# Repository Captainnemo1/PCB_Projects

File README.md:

# PCB_Projects
This repo consists of various PCBs made by me 
They have been labeled as per the name of the project

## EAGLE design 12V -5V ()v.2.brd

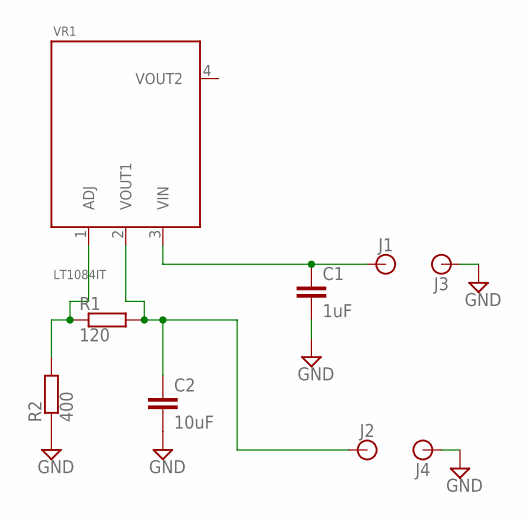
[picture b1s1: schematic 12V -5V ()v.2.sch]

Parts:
C1: 1uF; C0805
C2: 10uF; C0805
J1, J2, J3, J4: BANANA_CONN
R1: 120; R0805
R2: 400; R0805
VR1: LT1084IT

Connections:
GND: C1.2, C2.2, J3.P$1, J4.P$1, R2.1
unnamed: R1.1, R2.2, VR1.1 (ADJ)
VIN: C1.1, J1.P$1, VR1.3 (VIN)
VOUT: C2.1, J2.P$1, R1.2, VR1.2 (VOUT1)

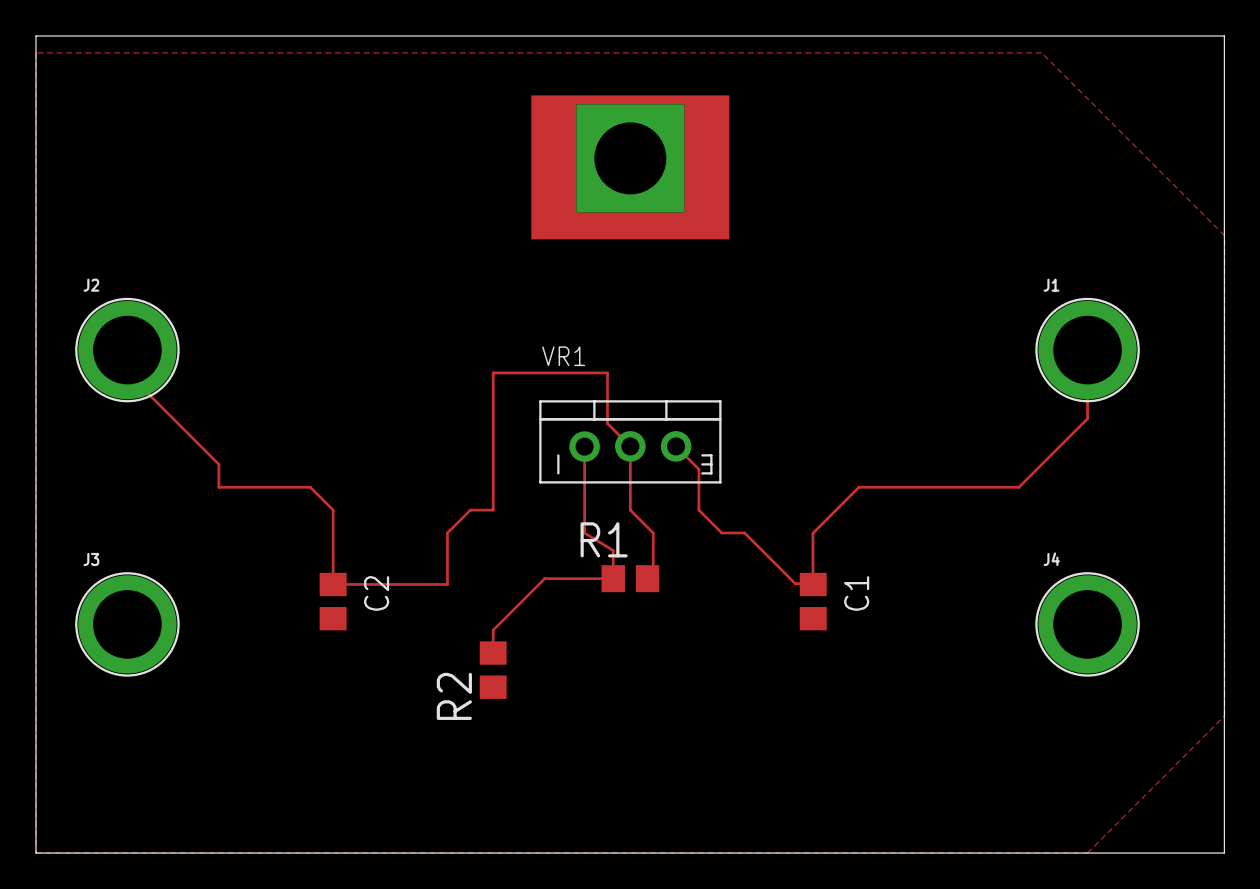
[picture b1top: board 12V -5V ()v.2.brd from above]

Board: 2 copper layers, 66.0 x 45.4 mm, 9 parts (0 on the bottom side), 4 nets.

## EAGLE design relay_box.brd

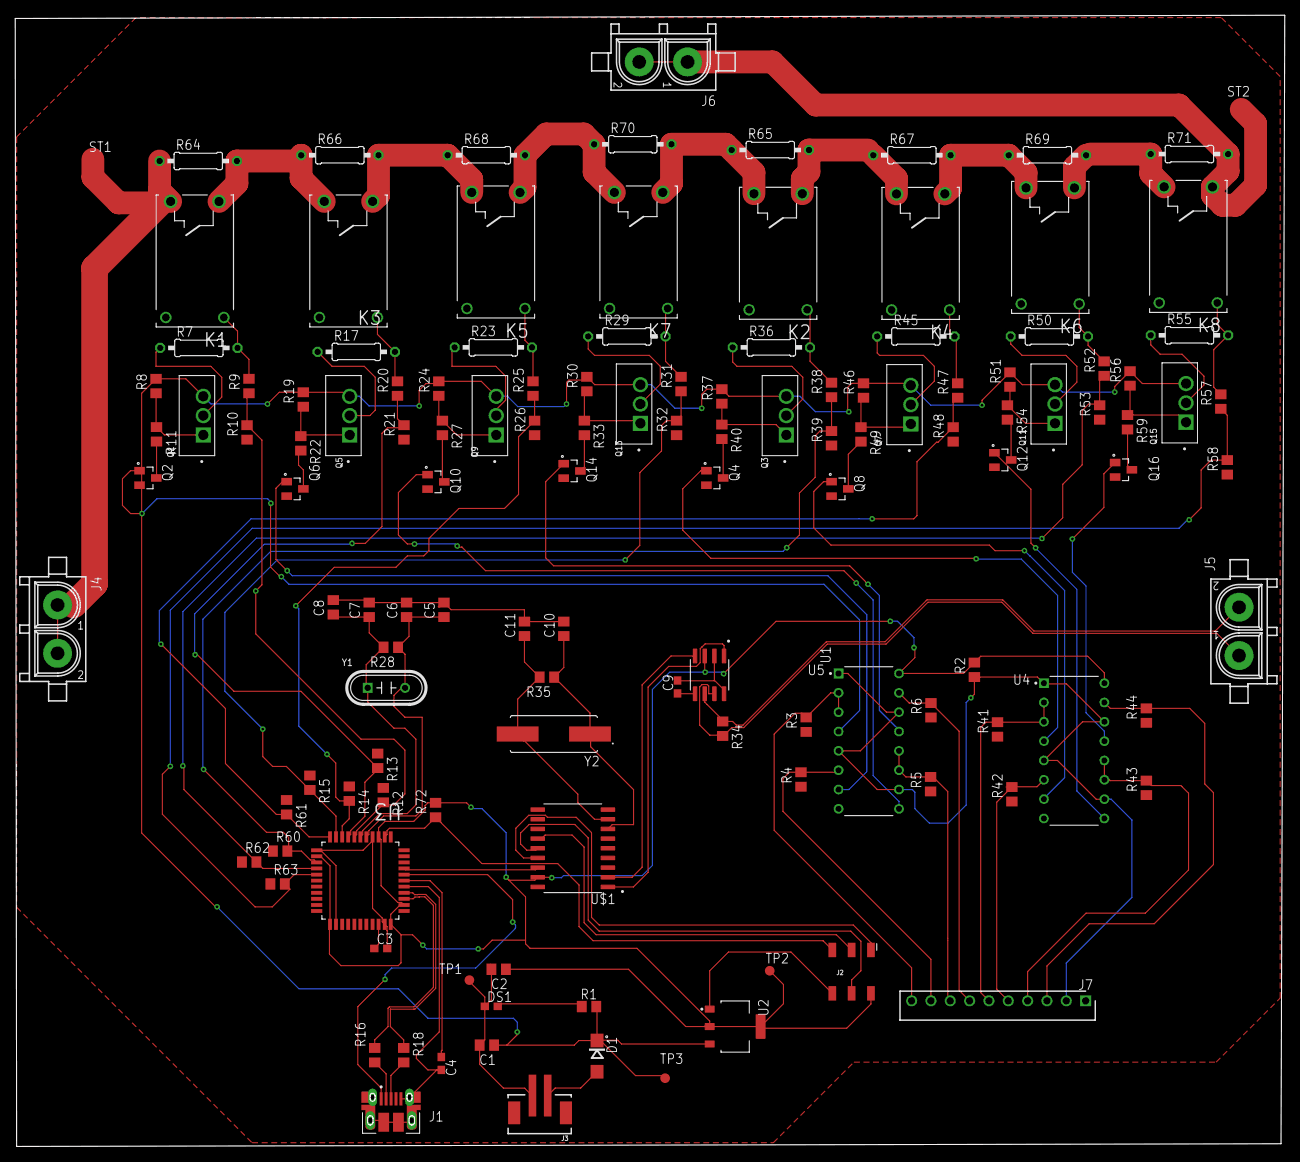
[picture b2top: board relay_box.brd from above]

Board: 2 copper layers, 166.8 x 148.6 mm, 129 parts (0 on the bottom side), 93 nets.

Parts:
C1, C2, C5, C6, C7, C8, C10, C11: 10uF; C0805
C3, C4: 1uF; C0603
C9: 22uF; C0603
D1: SS12-TP; DO214AC
DS1: LTST-C190TBKT; 0603
J1: 10103594-0001LF; AMPHENOL_10103594-0001LF
J2: 2X3_SMD
J3: JST-2-SMD-VERT
J4, J5, J6: 350428-1
J7: 5-534237-8; RHDR10W76P0X254_1X10_2540X356X
K1, K2, K3, K4, K5, K6, K7, K8: JV-5S-KT; JV-KT
Q1, Q3, Q5, Q7, Q9, Q11, Q13, Q15: IRF9540; TO254P1052X465X1989-3
Q2, Q4, Q6, Q8, Q10, Q12, Q14, Q16: MMBT3904LT1G; SOT23
R1: 560R; R0805
R2, R3, R4, R5, R6, R12, R13, R14, R15, R41, R42, R43, R44, R60, R61, R62, R63, R72: 10k; R0805
R7, R17, R23, R29, R36, R45, R50, R55: 560R; 0207/10
R8, R10, R19, R21, R24, R26, R30, R32, R37, R39, R46, R48, R51, R53, R56, R58: 12K; R0805
R9, R11, R20, R22, R25, R27, R31, R33, R38, R40, R47, R49, R52, R54, R57, R59: 18K; R0805
R16, R18: 22R; R0805
R28, R35: 1M; R0805
R34: 120R; R0805
R64, R65, R66, R67, R68, R69, R70, R71: 0R; 0207/10
ST1, ST2: TPB1,27; B1,27
TP1, TP2, TP3: TPB1,27; B1,27
U1: TJA1050T/CM,118; SOIC127P600X175-8N
U2: AMS1117-5.0; SOT229P700X180-4N
U3: ATMEGA32U4-AU; QFP80P1200X1200X120-44N
U4, U5: SN74LS279AN; DIP794W45P254L1969H508Q16
U$1: MCP2515-I/SO; SOIC127P1030X265-18N
Y1: 49S/18PF; XTAL_49S/18PF
Y2: FOXSDLF/080-20; XTAL1170X500X450

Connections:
1Q: Q2.1, U5.4
1S: J7.10, R3.2, U5.2, U5.3
2Q: Q6.1, U5.7
2S: J7.9, R4.2, U5.6
3Q: Q10.1, U5.9
3S: J7.8, R5.2, U5.11, U5.12
4Q: Q14.1, U5.13
4S: J7.7, R6.2, U5.15
5Q: Q4.1, U4.4
5S: J7.6, R41.2, U4.2, U4.3
6Q: Q8.1, U4.7
6S: J7.5, R42.2, U4.6
7Q: Q12.1, U4.9
7S: J7.4, R43.2, U4.11, U4.12
8Q: Q16.1, U4.13
8S: J7.3, R44.2, U4.15
+5V: C2.1, J2.2, R2.2, R72.2, TP2.TP, U1.3, U2.2, U2.4, U3.2, U3.14, U3.24, U3.34, U3.44, U4.16, U5.16, U$1.17
CAN_N: J5.2, R34.1, U1.6
CAN_P: J5.1, R34.2, U1.7
D_N: R16.1, U3.3
D_P: R18.1, U3.4
GND: C1.2, C2.2, C3.2, C5.2, C6.2, C7.2, C8.2, C9.2, C10.2, C11.2, DS1.1, J2.6, J3.GND, K1.4, K2.4, K3.4, K4.4, K5.4, K6.4, K7.4, K8.4, Q2.2, Q4.2, Q6.2, Q8.2, Q10.2, Q12.2, Q14.2, Q16.2, R3.1, R4.1, R5.1, R6.1, R10.1, R12.1, R13.1, R14.1, R15.1, R21.1, R26.1, R32.1, R39.1, R41.1, R42.1, R43.1, R44.1, R48.1, R53.1, R58.1, R60.1, R61.1, R62.1, R63.1, TP1.TP, U1.2, U1.8, U2.1, U3.15, U3.23, U3.35, U3.43, U4.8, U5.8, U$1.9
HVD: J4.1, J4.2, K1.3, R64.1, ST1.TP
MISO: J2.1, U$1.15
MOSI: J2.4, U$1.14
unnamed: Q1.1, R8.1, R11.1
unnamed: Q1.2, R7.1
unnamed: Q2.3, R11.2
unnamed: K1.1, R7.2, R9.2
unnamed: Q3.1, R37.1, R40.1
unnamed: Q4.3, R40.2
unnamed: K2.1, R36.2, R38.2
unnamed: Q3.2, R36.1
unnamed: Q5.1, R19.1, R22.1
unnamed: Q6.3, R22.2
unnamed: K3.1, R17.2, R20.2
unnamed: Q5.2, R17.1
unnamed: Q7.1, R46.1, R49.1
unnamed: Q8.3, R49.2
unnamed: K4.1, R45.2, R47.2
unnamed: Q7.2, R45.1
unnamed: Q9.1, R24.1, R27.1
unnamed: Q10.3, R27.2
unnamed: K5.1, R23.2, R25.2
unnamed: Q9.2, R23.1
unnamed: Q11.1, R51.1, R54.1
unnamed: Q12.3, R54.2
unnamed: K6.1, R50.2, R52.2
unnamed: Q11.2, R50.1
unnamed: Q13.1, R30.1, R33.1
unnamed: Q14.3, R33.2
unnamed: K7.1, R29.2, R31.2
unnamed: Q13.2, R29.1
unnamed: Q15.1, R56.1, R59.1
unnamed: Q16.3, R59.2
unnamed: K8.1, R55.2, R57.2
unnamed: Q15.2, R55.1
unnamed: DS1.2, R1.1
unnamed: D1.A, J3.VCC
unnamed: J1.2, R16.2
unnamed: J1.3, R18.2
unnamed: C9.1, U1.5
unnamed: C3.1, U3.42
OSC1: C11.1, R35.2, U$1.8, Y2.2
OSC2: C10.1, R35.1, U$1.7, Y2.1
PD0: R9.1, R10.2, R12.2, U3.18
PD1: R13.2, R20.1, R21.2, U3.19
PD2: R14.2, R25.1, R26.2, U3.20
PD3: R15.2, R31.1, R32.2, U3.21
PD4: R38.1, R39.2, R60.2, U3.25
PD5: R47.1, R48.2, R61.2, U3.22
PD6: R52.1, R53.2, R62.2, U3.26
PD7: R57.1, R58.2, R63.2, U3.27
R: J7.2, R2.1, U4.1, U4.5, U4.10, U4.14, U5.1, U5.5, U5.10, U5.14
RELAY1: K1.2, K3.3, R64.2, R66.1
RELAY2: K3.2, K5.3, R66.2, R68.1
RELAY3: K5.2, K7.3, R68.2, R70.1
RELAY4: K2.3, K7.2, R65.1, R70.2
RELAY5: K2.2, K4.3, R65.2, R67.1
RELAY6: K4.2, K6.3, R67.2, R69.1
RELAY7: K6.2, K8.3, R69.2, R71.1
RELAY8: J6.1, J6.2, K8.2, R71.2, ST2.TP
RST: J2.5, R72.1, U3.13
RX_CAN: U1.4, U$1.2
SCLK: J2.3, U$1.13
SS: U3.8, U$1.16
TX_CAN: U1.1, U$1.1
UCAP: C4.1, U3.6
UGND: C4.2, J1.5, J1.6, J1.7, J1.8, J1.9, J1.10, J1.11, J1.S1, J1.S2, U3.5
VBUS: J1.1, U3.7
VCC: C1.1, D1.C, Q1.3, Q3.3, Q5.3, Q7.3, Q9.3, Q11.3, Q13.3, Q15.3, R1.2, R8.2, R19.2, R24.2, R30.2, R37.2, R46.2, R51.2, R56.2, TP3.TP, U2.3
XTAL1: C7.1, C8.1, R28.2, U3.17, Y1.1
XTAL2: C5.1, C6.1, R28.1, U3.16, Y1.2

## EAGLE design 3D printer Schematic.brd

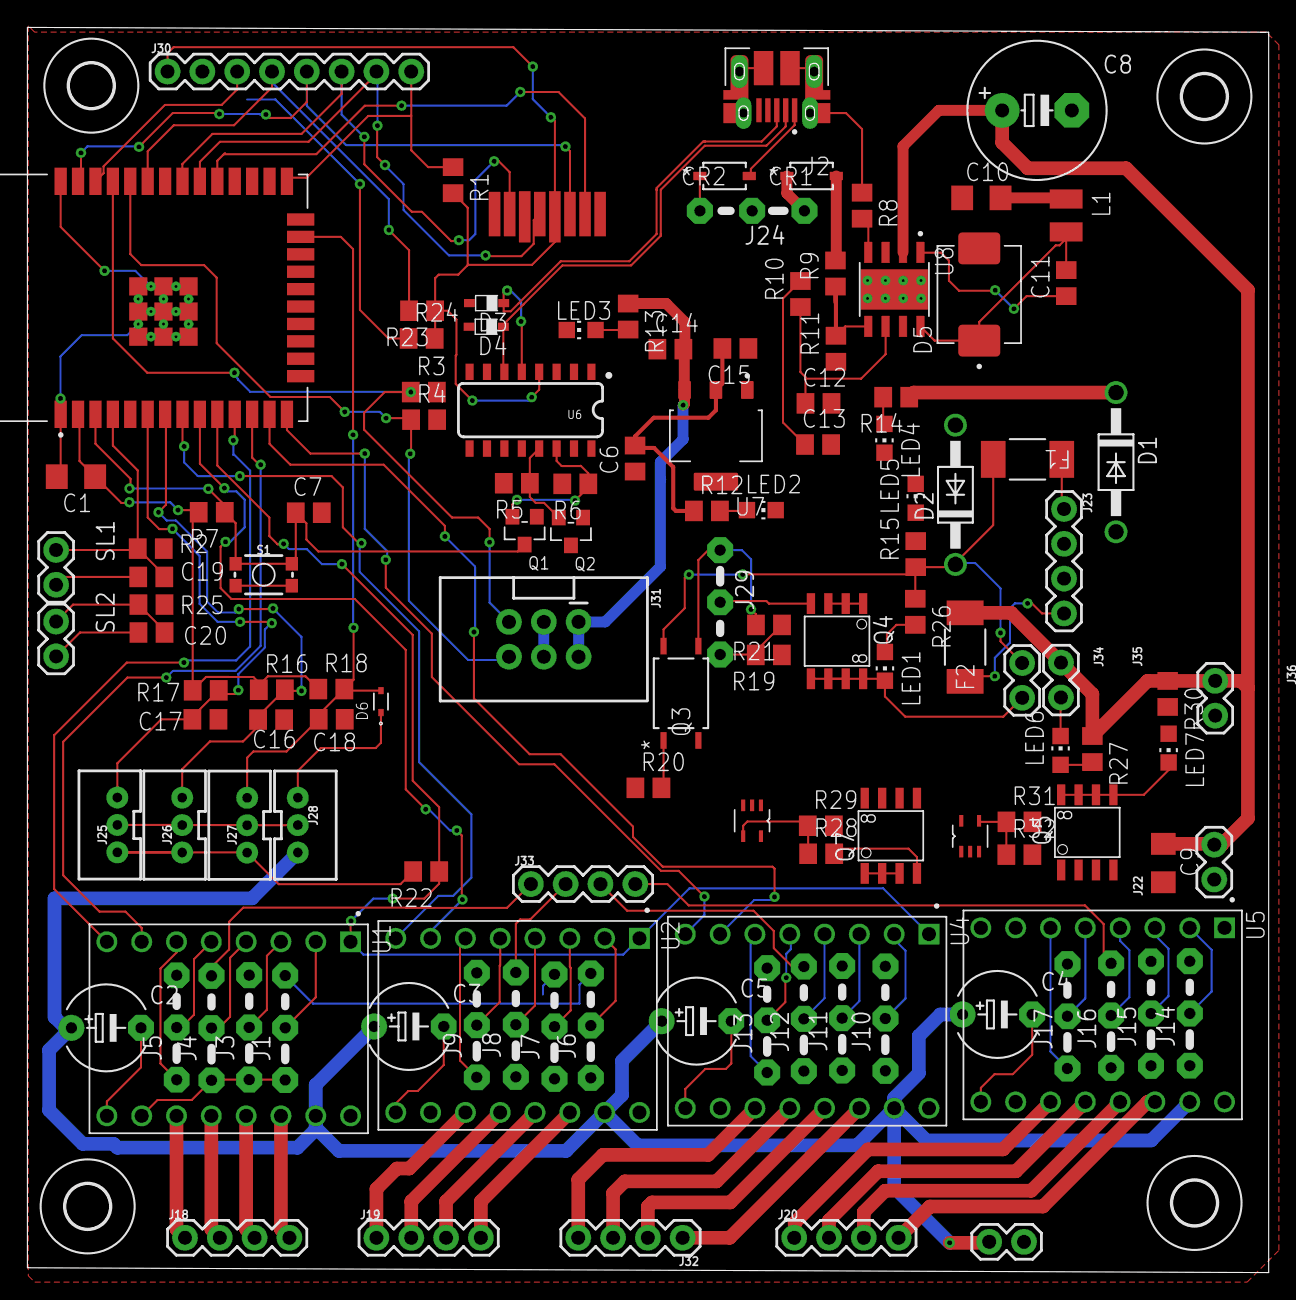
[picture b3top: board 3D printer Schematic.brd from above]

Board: 2 copper layers, 90.6 x 90.9 mm, 130 parts (1 on the bottom side), 112 nets.

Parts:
A1, A2: 74LVC1G125DCKRG4; DCK5_TEX
B2: MICRO-SDCARD
C1: 100uF 6.3V; C1206
C2, C3, C4, C5: 100uF35V; E5-6
C6: 10nF50V; C0805
C7: 100uF25V; C0805
C8: 100uF50V; E5-10,5
C9: 4.7uF50V; C1206
C10: 47uF16V; C1206
C11: 100nF50V; C0805
C12: 56pF50V; C0805
C13: 820pF50V; C0805
C14, C15: 47uF6.3V; C0805
C16, C17, C18: 100nF25V; C0805
C19, C20: 22uF6.3V; C0805
CR1, CR2: CR_19WLC_LTO
D1, D2: 1N4004; DO41-10
D3, D4: PESD5V0S1BA; SOD323
D5: B540C-13-F; DIOM6959X245N
D6: 1N4148WT; SODFL1608X70N
F1: 15A 2410; 0453SERIES_LTF
F2: 30A 3912; 0453SERIES_LTF
H1, H2, H3, H4: MOUNT-HOLE3.2; 3,2
J1, J3, J4, J5, J6, J7, J8, J9, J10, J11, J12, J13, J14, J15, J16, J17, J24, J29: 04C
J2: 10103594-0001LF; AMPHENOL_10103594-0001LF
J18, J19, J20, J23: 1X04
J21: Fan_case; 1X02
J22: FAN_HEATSINK; 1X02
J25, J26, J27, J28: JST-3-PTH-VERT
J30: 1X08
J31: 2X3-SHROUDED
J32: Z_Motor; 1X04
J33: CS_PINS; 1X04
J34: BED; 1X02
J35: E0; 1X02
J36: PART_FAN; 1X02
L1: 4.7uH4.5A; L2825P
LED1: LED_BED; CHIP-LED0805
LED2: LED_3V; CHIP-LED0805
LED3: LED_5V; CHIP-LED0805
LED4: LED_VIN; CHIP-LED0805
LED5: LED_VBED; CHIP-LED0805
LED6: LED_E0; CHIP-LED0805
LED7: LED_FAN; CHIP-LED0805
Q1, Q2: SMD-TRANSISTOR-NPN-50V-100MA(SOT-23); SOT-23
Q3: TLP182(E; 4PIN_SO6_TOS
Q4, Q5, Q7: FDS5680; SO-8
R1, R16, R17, R18, R22, R23, R24: 10K; R0805
R2, R25: 4.7K; R0805
R3, R4: 0R; R0805
R5, R6, R7: 12K; R0805
R8, R12, R13, R14, R15: 73.2K; R0805
R9: 60.4K; R0805
R10: 23.7K; R0805
R11: 11.5K; R0805
R19, R21: 1K; R0805
R20: 330R; R0805
R26, R27, R30: 2.2K; R0805
R28, R31: 10R; R0805
R29, R32: 100K; R0805
S1: TACTILE_SWITCH_SMD_4.6X2.8MM
SL1: T_E0; 1X02
SL2: T_BED; 1X02
U1, U2, U4, U5: A4988_STEPPER_MOTOR_DRIVER_CARRIER; MODULE_A4988_STEPPER_MOTOR_DRIVER_CARRIER
U3: ESP32-WROOM-32D; MODULE_ESP32-WROOM-32D
U6: CH340C; SO016
U7: AMS1117-3.3; SOT229P700X180-4N
U8: TPS54340DDA; VREG_LM5017MR/NOPB

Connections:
0: D1.A, J23.2, R19.1
3.3V: B2.VCC, C1.1, C6.2, C15.2, J1.1, J3.1, J4.1, J6.1, J7.1, J8.1, J10.1, J11.1, J12.1, J14.1, J15.1, J16.1, J25.1, J26.1, J27.1, J30.1, R1.2, R7.2, R12.1, R16.1, R17.1, R18.1, R22.2, R23.1, R24.2, U1.10, U2.10, U3.2, U4.10, U5.10, U6.4, U6.16, U7.2
5V1: C10.2, CR1.2, L1.1, R9.2
+5V: A1.5, A2.5, C14.2, J24.2, J31.1, J31.2, R2.2, R13.1, R25.2, U7.3
COMP: C12.1, R10.1, U8.6
DTR: Q2.2, R5.1, U6.13
D_N: D4.C, J2.2, U6.6
D_P: D3.C, J2.3, U6.5
E0_CS: J16.3, J33.4
E0_DIR_PIN: U3.28, U5.8
E0_MS1: J14.2, U5.2
E0_MS2: J15.2, U5.3
E0_MS3: J16.2, U5.4
E0_RST: J17.2, U5.5
E0_SLP: J17.1, U5.6
E0_STEP_PIN: U3.27, U5.7
EN: C7.1, Q1.3, R7.1, S1.3, S1.4, U3.3
FAN_E0_PIN: A2.2, U3.16
FB: R9.1, R11.2, U8.5
GND: A1.1, A1.3, A2.1, A2.3, B2.GND, C1.2, C2.-, C3.-, C4.-, C5.-, C6.1, C7.2, C8.-, C9.2, C10.1, C12.2, C13.2, C14.1, C15.1, C16.2, C17.2, C18.2, C19.1, C20.1, D2.A, D3.A, D4.A, D5.A, J2.5, J2.6, J2.7, J2.8, J2.9, J2.10, J2.11, J2.S1, J2.S2, J21.1, J22.1, J23.3, J25.2, J26.2, J27.2, J28.2, J31.3, J31.4, LED2.C, LED3.C, LED4.C, LED5.C, Q3.3, Q4.1, Q4.2, Q4.3, Q5.1, Q5.2, Q5.3, Q7.1, Q7.2, Q7.3, R8.1, R11.1, R29.2, R32.2, S1.1, S1.2, SL1.2, SL2.2, U1.9, U1.16, U2.9, U2.16, U3.1, U3.15, U3.38, U3.39_1, U3.39_2, U3.39_3, U3.39_4, U3.39_5, U3.39_6, U3.39_7, U3.39_8, U3.39_9, U3.39_10, U3.39_11, U3.39_12, U3.39_13, U3.39_14, U3.39_15, U3.39_16, U3.39_17, U3.39_18, U3.39_19, U3.39_20, U3.39_21, U4.9, U4.16, U5.9, U5.16, U6.1, U7.1, U8.7, U8.9
HEATER_BED_PIN: R20.1, U3.26
HEATER_E0_PIN: A1.2, U3.24
IO0: J30.8, Q2.3, R1.1, U3.25
MISO: B2.DAT0, J5.3, J9.3, J13.3, J17.3, J30.6, U3.31
MOSI: B2.CMD, J1.3, J6.3, J10.3, J14.3, J30.5, U3.37
MOTOR_EN_PIN: R22.1, U1.1, U2.1, U3.10, U4.1, U5.1
unnamed: J36.2, LED7.C, Q5.5, Q5.6, Q5.7, Q5.8
unnamed: LED7.A, R30.2
unnamed: J18.1, U1.11
unnamed: J18.2, U1.12
unnamed: J18.3, U1.13
unnamed: J18.4, U1.14
unnamed: Q1.1, R5.2
unnamed: Q2.1, R6.2
unnamed: F1.1, J23.1
unnamed: F2.1, J23.4
unnamed: LED2.A, R12.2
unnamed: R3.2, U6.3
unnamed: R4.2, U6.2
unnamed: R8.2, U8.4
unnamed: LED3.A, R13.2
unnamed: C13.1, R10.2
unnamed: C11.1, U8.1
unnamed: C11.2, D5.C, L1.2, U8.8
unnamed: LED4.A, R14.2
unnamed: J19.1, U2.11
unnamed: J19.2, U2.12
unnamed: J19.3, U2.13
unnamed: J19.4, U2.14
unnamed: J20.1, U5.11
unnamed: J20.2, U5.12
unnamed: J20.3, U5.13
unnamed: J20.4, U5.14
unnamed: LED5.A, R15.2
unnamed: CR1.1, J24.1
unnamed: CR2.1, J24.3
unnamed: D6.C, J28.1
unnamed: Q3.1, R20.2
unnamed: Q5.4, R31.2
unnamed: J29.1, Q3.4, R21.2
unnamed: LED1.A, R26.2
unnamed: J29.3, R19.2, R21.1
unnamed: J34.2, LED1.C, Q4.5, Q4.6, Q4.7, Q4.8
unnamed: LED6.A, R27.2
unnamed: J35.2, LED6.C, Q7.5, Q7.6, Q7.7, Q7.8
unnamed: Q7.4, R28.2
RTS: Q1.2, R6.1, U6.14
SCK: B2.CLK, J3.3, J7.3, J11.3, J15.3, J30.7, U3.30
SCL: J30.3, R24.1, U3.36
SDA: J30.4, R23.2, U3.33
SS: B2.CD/DAT3, U3.29
TEMP_BED_PIN: C20.2, R25.1, SL2.1, U3.5
TEMP_E0_PIN: C19.2, R2.1, SL1.1, U3.4
TO_FAN_E0: A2.4, R31.1, R32.1
TO_HEATER_BED: J29.2, Q4.4
TO_HEATER_E0: A1.4, R28.1, R29.1
UART+: J31.5, R3.1, U3.35
UART-: J31.6, R4.1, U3.34
VBED: D2.C, F1.2, J34.1, Q3.6, R15.1, R26.1
VIN: C2.+, C3.+, C4.+, C5.+, C8.+, C9.1, D1.C, F2.2, J21.2, J22.2, J28.3, J35.1, J36.1, R14.1, R27.1, R30.1, U1.15, U2.15, U4.15, U5.15, U8.2
VUSB: CR2.2, J2.1
X_CS: J4.3, J33.1
X_DIR_PIN: U1.8, U3.11
X_MIN: C17.1, J25.3, R17.2, U3.6
X_MS1: J1.2, U1.2
X_MS2: J3.2, U1.3
X_MS3: J4.2, U1.4
X_RST: J5.2, U1.5
X_SLP: J5.1, U1.6
X_STEP_PIN: U1.7, U3.12
Y_CS: J8.3, J33.2
Y_DIR_PIN: U2.8, U3.8
Y_MIN: C16.1, J26.3, R16.2, U3.7
Y_MS1: J6.2, U2.2
Y_MS2: J7.2, U2.3
Y_MS3: J8.2, U2.4
Y_RST: J9.2, U2.5
Y_SLP: J9.1, U2.6
Y_STEP_PIN: U2.7, U3.9
Z_1A: J32.4, U4.11
Z_1B: J32.3, U4.12
Z_2A: J32.2, U4.13
Z_2B: J32.1, U4.14
Z_CS: J12.3, J33.3
Z_DIR_PIN: U3.14, U4.8
Z_MIN: C18.1, D6.A, J27.3, R18.2, U3.23
Z_MS1: J10.2, U4.2
Z_MS2: J11.2, U4.3
Z_MS3: J12.2, U4.4
Z_RST: J13.2, U4.5
Z_SLP: J13.1, U4.6
Z_STEP_PIN: U3.13, U4.7

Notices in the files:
parts and their libraries:
SparkFun-Connectors: Licensing: Creative Commons ShareAlike 4.0 International - https://creativecommons.org/licenses/by-sa/4.0
COPYRIGHT: Copyright (C) 2021 Ultra Librarian. All rights reserved.
